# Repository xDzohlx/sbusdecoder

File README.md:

# sbusdecoder
Decodificador para receptor de radio con sbus, ppm, ibus

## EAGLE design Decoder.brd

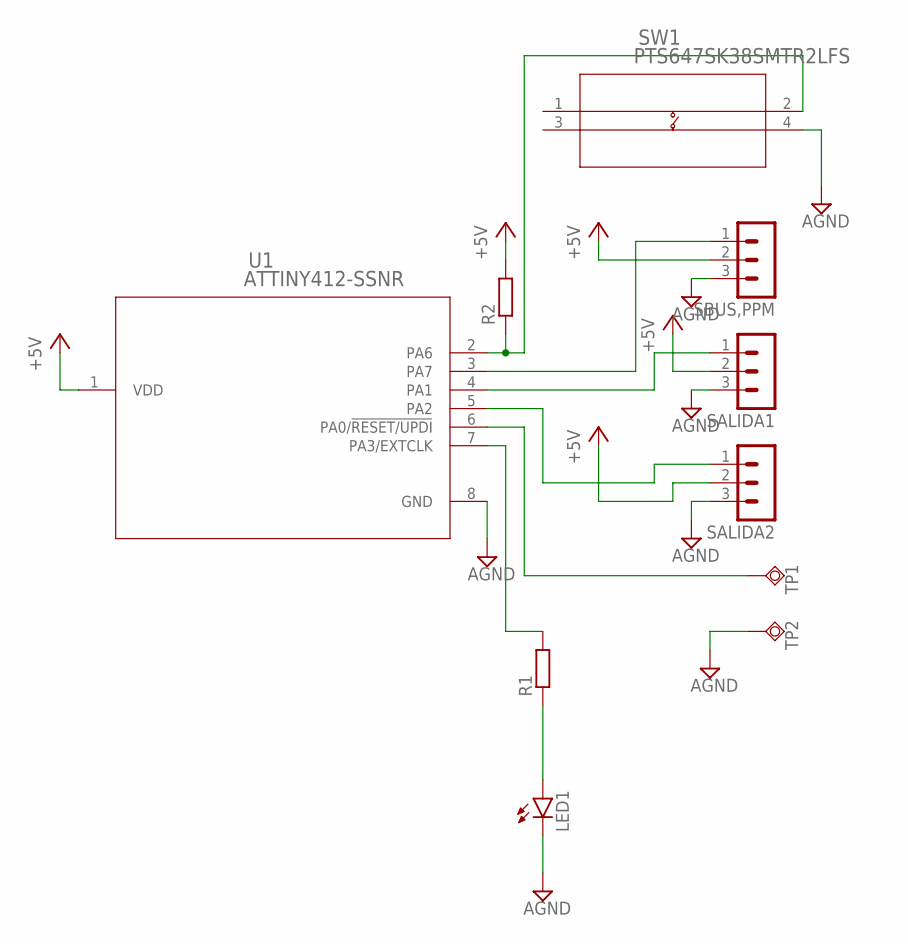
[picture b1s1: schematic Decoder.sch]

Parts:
LED1: LEDCHIPLED_0603; CHIPLED_0603
R1, R2: R-EU_R0805; R0805
SALIDA1, SALIDA2: MA03-1
SBUS,PPM: MA03-1
SW1: PTS647SK38SMTR2LFS; PTS647SK38SMTR2LFS_CNK
TP1, TP2: TPSQTP13R; TP13R
U1: ATTINY412-SSNR; SOIC8_SA_SST_MCH

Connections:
+5V: R2.2, SALIDA1.2, SALIDA2.2, SBUS,PPM.2, U1.1 (VDD)
AGND: LED1.C, SALIDA1.3, SALIDA2.3, SBUS,PPM.3, SW1.4, TP2.TP, U1.8 (GND)
unnamed: TP1.TP, U1.6 (PA0/!RESET/UPDI)
unnamed: SBUS,PPM.1, U1.3 (PA7)
unnamed: SALIDA1.1, U1.4 (PA1)
unnamed: SALIDA2.1, U1.5 (PA2)
unnamed: R1.2, U1.7 (PA3/EXTCLK)
unnamed: R2.1, SW1.2, U1.2 (PA6)
unnamed: LED1.A, R1.1

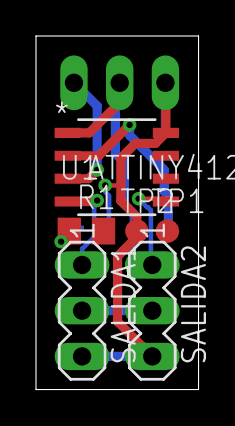
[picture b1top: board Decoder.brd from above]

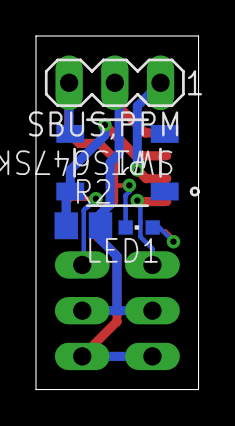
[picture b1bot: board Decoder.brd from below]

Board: 2 copper layers, 9.0 x 19.6 mm, 10 parts (4 on the bottom side), 9 nets.

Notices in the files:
parts and their libraries:
COPYRIGHT: Copyright (C) 2018 Accelerated Designs. All rights reserved
